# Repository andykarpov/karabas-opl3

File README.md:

## Karabas-OPL3

Simple OPL3 sound card for ZX Spectrum (NemoBus). 
Inspired by a BomgeMoon soundcard :)

### Tech specs

* OPL3 sound by YMF-262-M
* 16-bit DAC UDA1334A
* EPM3128 CPLD
* Low profile PCB: 92x44mm (standard) and 131x44mm (xxl version)
* 5V only power required

### Changelog & current status

* Rev.A - initial release
* Rev.B - reduced pcb size, removed config switch

### Related projects

* BomgeMoon - [link](https://github.com/Kulicheg/BomgeMoon)
* ZX-Multisound - [link](https://github.com/UzixLS/zx-multisound)
* Turbo Sound FM - [link](http://www.nedopc.com/TURBOSOUND/ts-fm.php)
* ZXM-SoundCard - [link](http://micklab.ru/My%20Soundcard/ZXMSoundCard.htm)
* ZXM-GeneralSound - [link](http://micklab.ru/My%20Soundcard/ZXMGeneralSound.htm)
* NeoGS - [link](http://www.nedopc.com/gs/ngs.php)

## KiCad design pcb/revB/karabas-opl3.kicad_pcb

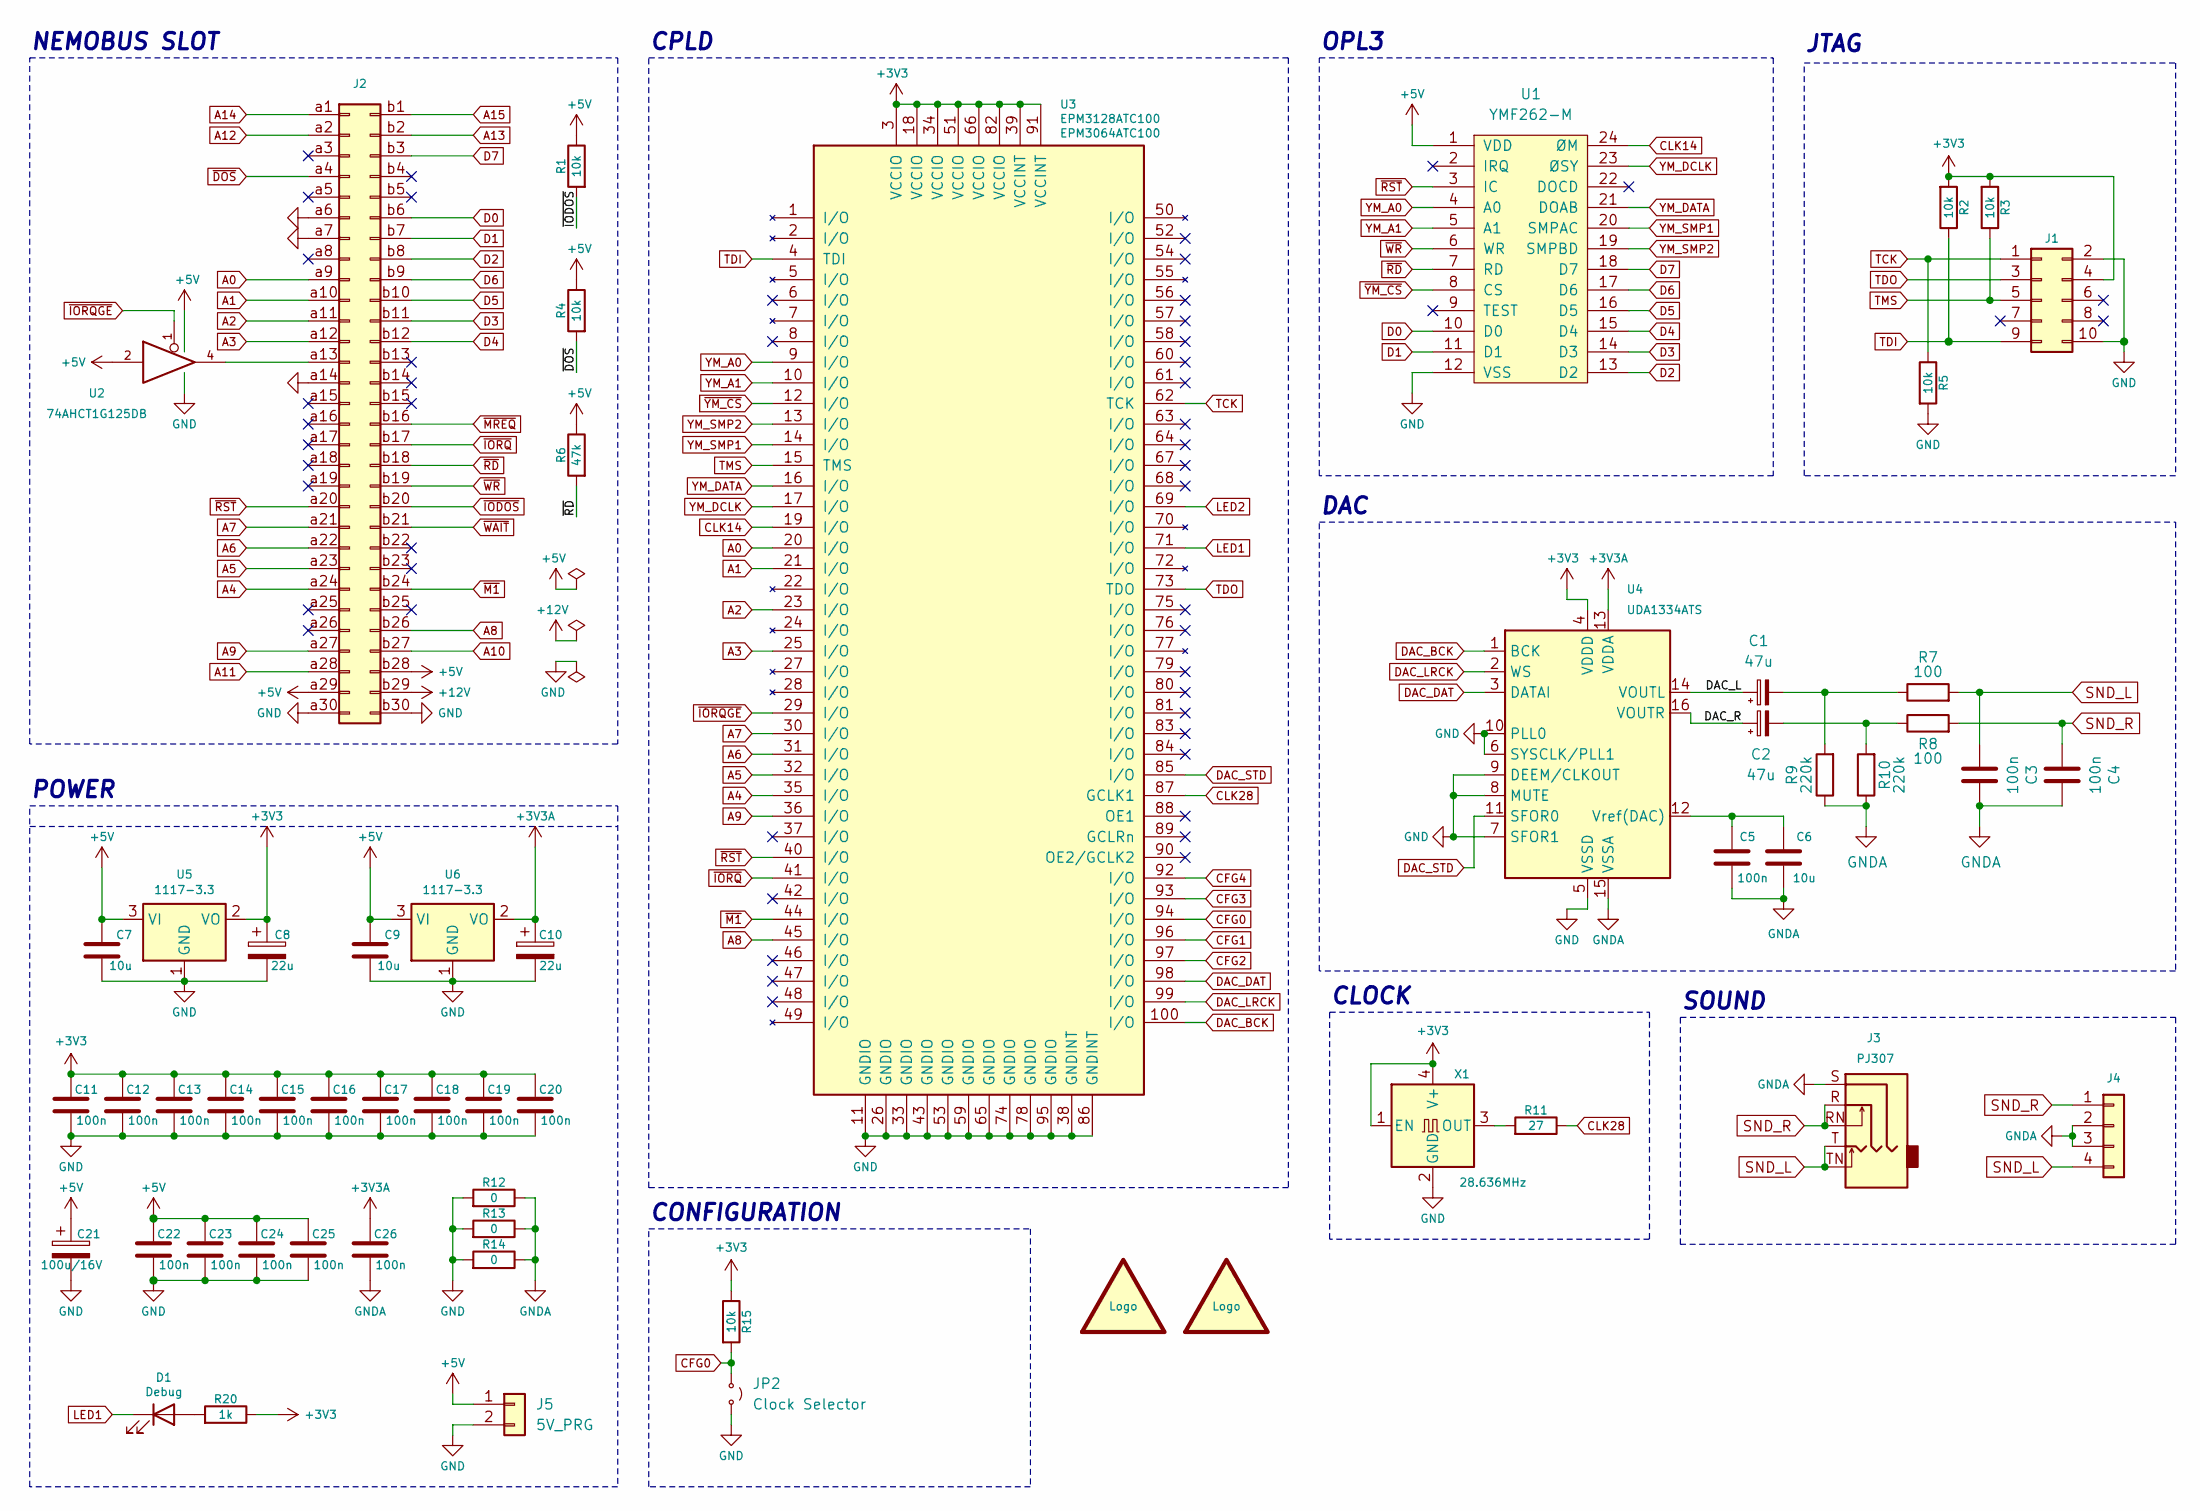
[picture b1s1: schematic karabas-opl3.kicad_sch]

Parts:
C1, C2: 47u; CP_Elec_5x5.9
C3, C4, C5, C11, C12, C13, C14, C15, C16, C17, C18, C19, C20, C22, C23, C24, C25, C26: 100n; C_0805_2012Metric_Pad1.18x1.45mm_HandSolder
C6, C7, C9: 10u; C_0805_2012Metric_Pad1.18x1.45mm_HandSolder
C8, C10: 22u; CP_EIA-3216-18_Kemet-A_HandSolder
C21: 100u/16V; CP_Elec_6.3x7.7
D1: Debug; LED_0805_2012Metric_Pad1.15x1.40mm_HandSolder
J1: Conn_02x05_Odd_Even; PinHeader_2x05_P2.54mm_Vertical
J2: Conn_02x30_Row_Letter_First; ZX_NEMO_60_EDGE
J3: PJ307; PJ-307
J4: Conn_01x04; PinHeader_1x04_P2.54mm_Vertical
J5: 5V_PRG; PinHeader_1x02_P2.54mm_Vertical
JP2: Clock Selector; SolderJumper-2_P1.3mm_Open_TrianglePad1.0x1.5mm
LOGO1: graphic; opl3
LOGO2: graphic; andy_karpov_logo4_silk
R1, R2, R3, R4, R5, R15: 10k; R_0805_2012Metric_Pad1.20x1.40mm_HandSolder
R6: 47k; R_0805_2012Metric_Pad1.20x1.40mm_HandSolder
R7, R8: 100; R_0805_2012Metric_Pad1.20x1.40mm_HandSolder
R9, R10: 220k; R_0805_2012Metric_Pad1.20x1.40mm_HandSolder
R11: 27; R_0805_2012Metric_Pad1.20x1.40mm_HandSolder
R12, R13, R14: 0; R_0805_2012Metric_Pad1.20x1.40mm_HandSolder
R20: 1k; R_0805_2012Metric_Pad1.20x1.40mm_HandSolder
U1: YMF262-M; ymf-262-m
U2: 74AHCT1G125DB; SOT-23-5_HandSoldering
U3: EPM3128ATC100; TQFP-100_14x14mm_P0.5mm
U4: UDA1334ATS; SSOP-16_4.4x5.2mm_P0.65mm-extended
U5, U6: 1117-3.3; SOT-223-3_TabPin2
X1: 28.636MHz; Oscillator_SMD_7050_7.0x5.0mm_mixed_3225

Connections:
+3V3: C8.1, C11.1, C12.1, C13.1, C14.1, C15.1, C16.1, C17.1, C18.1, C19.2, C20.2, J1.4, R2.2, R3.2, R15.1, R20.1, U3.3 (VCCIO), U3.18 (VCCIO), U3.34 (VCCIO), U3.39 (VCCINT), U3.51 (VCCIO), U3.66 (VCCIO), U3.82 (VCCIO), U3.91 (VCCINT), U4.4 (VDDD), U5.2 (VO), X1.1 (EN), X1.4 (V+)
+3V3A: C10.1, C26.1, U4.13 (VDDA), U6.2 (VO)
+5V: C7.1, C9.1, C21.1, C22.2, C23.2, C24.2, C25.2, J2.a29, J2.b28, J5.1, R1.1, R4.1, R6.1, U1.1 (VDD), U2.2, U2.5 (VCC), U5.3 (VI), U6.3 (VI)
+12V: J2.b29
/DAC_L: C1.1, U4.14 (VOUTL)
/DAC_R: C2.1, U4.16 (VOUTR)
A0: J2.a9, U3.20 (I/O)
A1: J2.a10, U3.21 (I/O)
A2: J2.a11, U3.23 (I/O)
A3: J2.a12, U3.25 (I/O)
A4: J2.a24, U3.35 (I/O)
A5: J2.a23, U3.32 (I/O)
A6: J2.a22, U3.31 (I/O)
A7: J2.a21, U3.30 (I/O)
A8: J2.b26, U3.45 (I/O)
A9: J2.a27, U3.36 (I/O)
A10: J2.b27
A11: J2.a28
A12: J2.a2
A13: J2.b2
A14: J2.a1
A15: J2.b1
CFG0: JP2.1 (A), R15.2, U3.94 (I/O)
CFG1: U3.96 (I/O)
CFG2: U3.97 (I/O)
CFG3: U3.93 (I/O)
CFG4: U3.92 (I/O)
CLK14: U1.24 (ØM), U3.19 (I/O)
CLK28: R11.1, U3.87 (GCLK1)
D0: J2.b6, U1.10 (D0)
D1: J2.b7, U1.11 (D1)
D2: J2.b8, U1.13 (D2)
D3: J2.b11, U1.14 (D3)
D4: J2.b12, U1.15 (D4)
D5: J2.b10, U1.16 (D5)
D6: J2.b9, U1.17 (D6)
D7: J2.b3, U1.18 (D7)
DAC_BCK: U3.100 (I/O), U4.1 (BCK)
DAC_DAT: U3.98 (I/O), U4.3 (DATAI)
DAC_LRCK: U3.99 (I/O), U4.2 (WS)
DAC_STD: U3.85 (I/O), U4.11 (SFOR0)
GND: C7.2, C8.2, C9.2, C10.2, C11.2, C12.2, C13.2, C14.2, C15.2, C16.2, C17.2, C18.2, C19.1, C20.1, C21.2, C22.1, C23.1, C24.1, C25.1, J1.2, J1.10, J2.a6, J2.a7, J2.a14, J2.a30, J2.b30, J5.2, JP2.2 (B), R5.2, R12.2, R13.2, R14.2, U1.12 (VSS), U2.3 (GND), U3.11 (GNDIO), U3.26 (GNDIO), U3.33 (GNDIO), U3.38 (GNDINT), U3.43 (GNDIO), U3.53 (GNDIO), U3.59 (GNDIO), U3.65 (GNDIO), U3.74 (GNDIO), U3.78 (GNDIO), U3.86 (GNDINT), U3.95 (GNDIO), U4.5 (VSSD), U4.6 (SYSCLK/PLL1), U4.7 (SFOR1), U4.8 (MUTE), U4.9 (DEEM/CLKOUT), U4.10 (PLL0), U5.1 (GND), U6.1 (GND), X1.2 (GND)
GNDA: C3.2, C4.2, C5.1, C6.1, C26.2, J3.S, J4.2, J4.3, R9.1, R10.1, R12.1, R13.1, R14.1, U4.15 (VSSA)
LED1: D1.1 (K), U3.71 (I/O)
LED2: U3.69 (I/O)
unnamed: C1.2, R7.1, R9.2
unnamed: C2.2, R8.1, R10.2
unnamed: D1.2 (A), R20.2
unnamed: J2.a13, U2.4
unnamed: C5.2, C6.2, U4.12 (Vref(DAC))
unnamed: R11.2, X1.3 (OUT)
SND_L: C3.1, J3.T, J3.TN, J4.4, R7.2
SND_R: C4.1, J3.R, J3.RN, J4.1, R8.2
TCK: J1.1, R5.1, U3.62 (TCK)
TDI: J1.9, R2.1, U3.4 (TDI)
TDO: J1.3, U3.73 (TDO)
TMS: J1.5, R3.1, U3.15 (TMS)
YM_A0: U1.4 (A0), U3.9 (I/O)
YM_A1: U1.5 (A1), U3.10 (I/O)
YM_DATA: U1.21 (DOAB), U3.16 (I/O)
YM_DCLK: U1.23 (ØSY), U3.17 (I/O)
YM_SMP1: U1.20 (SMPAC), U3.14 (I/O)
YM_SMP2: U1.19 (SMPBD), U3.13 (I/O)
~DOS: J2.a4, R4.2
~IODOS: J2.b20, R1.2
~IORQGE: U2.1, U3.29 (I/O)
~IORQ: J2.b17, U3.41 (I/O)
~M1: J2.b24, U3.44 (I/O)
~MREQ: J2.b16
~RD: J2.b18, R6.2, U1.7 (RD)
~RST: J2.a20, U1.3 (IC), U3.40 (I/O)
~WAIT: J2.b21
~WR: J2.b19, U1.6 (WR)
~YM_CS: U1.8 (CS), U3.12 (I/O)

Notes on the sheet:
SOUND
CPLD
DAC
CONFIGURATION
OPL3
JTAG
POWER
CLOCK
NEMOBUS SLOT

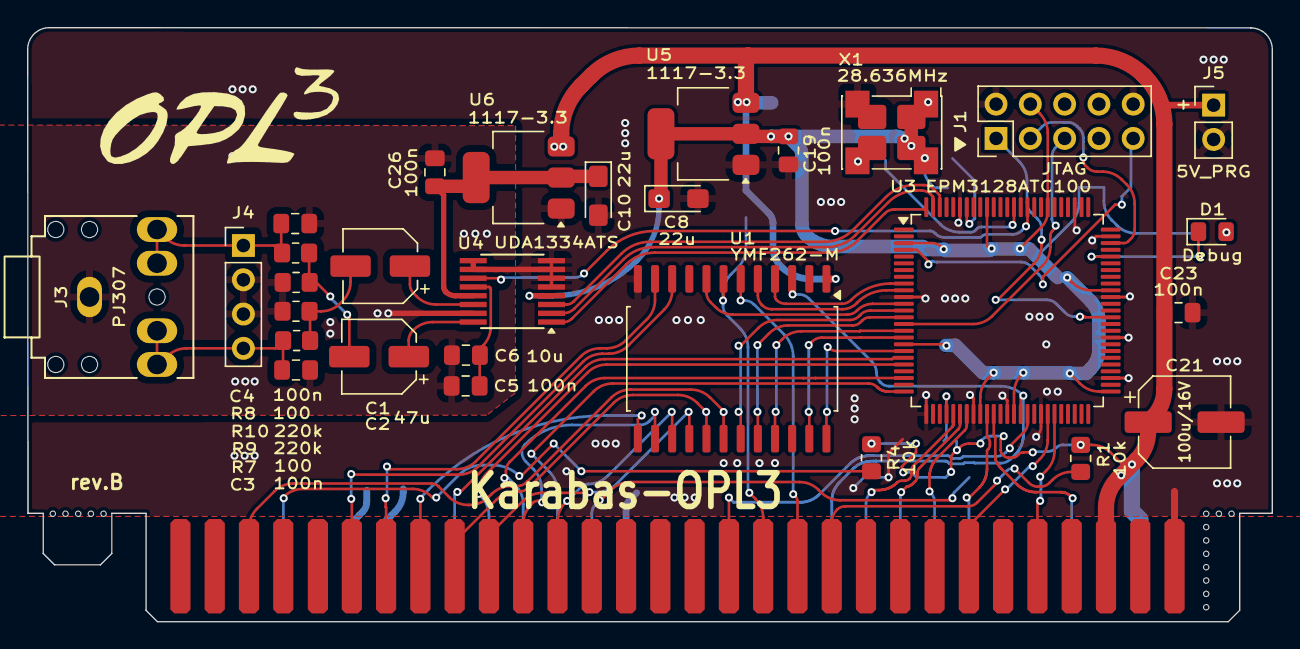
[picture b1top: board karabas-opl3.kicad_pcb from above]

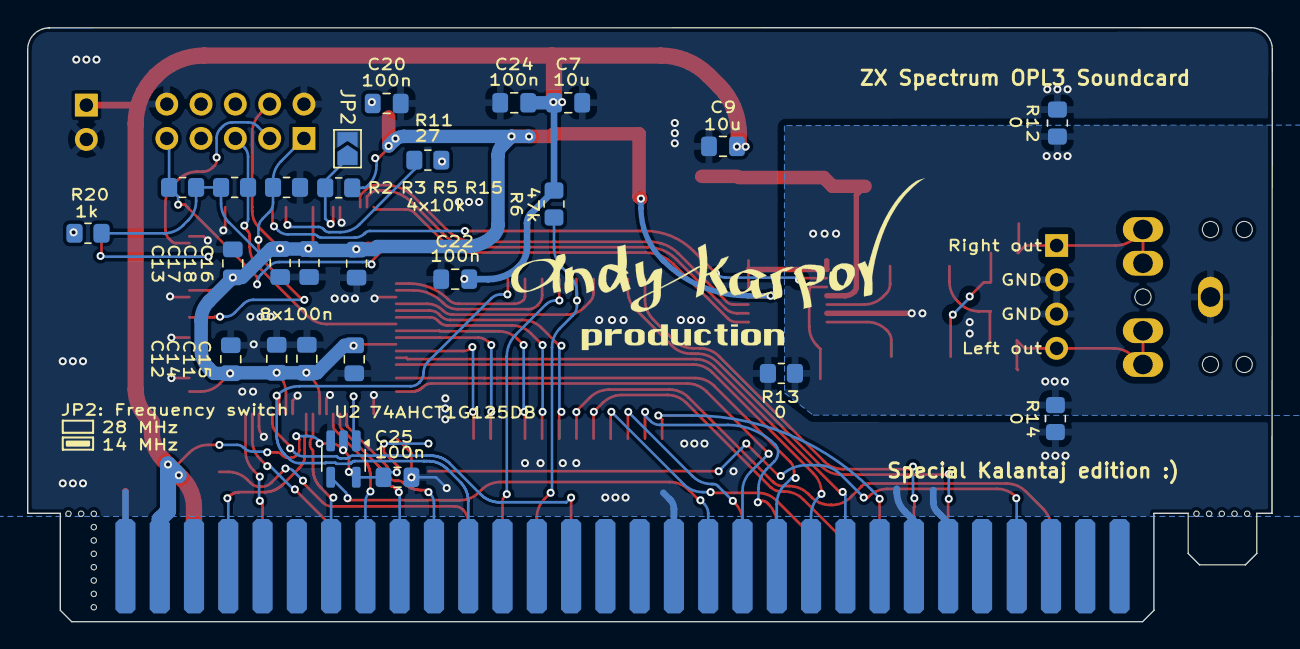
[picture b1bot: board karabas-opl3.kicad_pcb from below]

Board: 2 copper layers, 92.2 x 44.0 mm, 58 parts (27 on the bottom side), 60 nets.

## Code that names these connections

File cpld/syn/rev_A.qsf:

# -------------------------------------------------------------------------- #
#
# Copyright (C) 1991-2013 Altera Corporation
# Your use of Altera Corporation's design tools, logic functions 
# and other software and tools, and its AMPP partner logic 
# functions, and any output files from any of the foregoing 
# (including device programming or simulation files), and any 
# associated documentation or information are expressly subject 
# to the terms and conditions of the Altera Program License 
# Subscription Agreement, Altera MegaCore Function License 
# Agreement, or other applicable license agreement, including, 
# without limitation, that your use is for the sole purpose of 
# programming logic devices manufactured by Altera and sold by 
# Altera or its authorized distributors.  Please refer to the 
# applicable agreement for further details.
#
# -------------------------------------------------------------------------- #
#
# Quartus II 64-Bit
# Version 13.0.1 Build 232 06/12/2013 Service Pack 1 SJ Full Version
# Date created = 12:04:27  October 04, 2020
#
# -------------------------------------------------------------------------- #
#
# Notes:
#
# 1) The default values for assignments are stored in the file:
#		zx_multisound_assignment_defaults.qdf
#    If this file doesn't exist, see file:
#		assignment_defaults.qdf
#
# 2) Altera recommends that you do not modify this file. This
#    file is updated automatically by the Quartus II software
#    and any changes you make may be lost or overwritten.
#
# -------------------------------------------------------------------------- #


set_global_assignment -name FAMILY MAX3000A
set_global_assignment -name DEVICE "EPM3128ATC100-10"
set_global_assignment -name TOP_LEVEL_ENTITY karabas_opl3
set_global_assignment -name ORIGINAL_QUARTUS_VERSION "13.0 SP1"
set_global_assignment -name PROJECT_CREATION_TIME_DATE "12:04:27  OCTOBER 04, 2020"
set_global_assignment -name LAST_QUARTUS_VERSION "13.0 SP1"
set_global_assignment -name PROJECT_OUTPUT_DIRECTORY output
set_global_assignment -name DEVICE_FILTER_PIN_COUNT 144
set_global_assignment -name ERROR_CHECK_FREQUENCY_DIVISOR "-1"
set_global_assignment -name SDC_FILE clocks.sdc
set_global_assignment -name VERILOG_FILE ../rtl/top.v
set_global_assignment -name VHDL_INPUT_VERSION VHDL_2008
set_global_assignment -name VHDL_SHOW_LMF_MAPPING_MESSAGES OFF
set_global_assignment -name VERILOG_INPUT_VERSION VERILOG_2001
set_global_assignment -name VERILOG_SHOW_LMF_MAPPING_MESSAGES OFF
set_global_assignment -name MAX7000_DEVICE_IO_STANDARD "3.3-V LVTTL"
set_global_assignment -name SAVE_DISK_SPACE OFF
set_global_assignment -name TIMEQUEST_MULTICORNER_ANALYSIS OFF
set_global_assignment -name SYNTH_TIMING_DRIVEN_SYNTHESIS OFF

set_location_assignment PIN_9 -to ym_a[0]
set_location_assignment PIN_10 -to ym_a[1]
set_location_assignment PIN_12 -to n_ym_cs
set_location_assignment PIN_13 -to ym_smp[1]
set_location_assignment PIN_16 -to ym_data
set_location_assignment PIN_17 -to ym_dclk
set_location_assignment PIN_19 -to clk14
set_location_assignment PIN_20 -to a[0]
set_location_assignment PIN_21 -to a[1]
set_location_assignment PIN_23 -to a[2]
set_location_assignment PIN_29 -to n_iorqge
set_location_assignment PIN_30 -to a[7]
set_location_assignment PIN_31 -to a[6]
set_location_assignment PIN_32 -to a[5]
set_location_assignment PIN_35 -to a[4]
set_location_assignment PIN_36 -to a[9]
set_location_assignment PIN_41 -to n_iorq
set_location_assignment PIN_44 -to n_m1
set_location_assignment PIN_45 -to a[8]
set_location_assignment PIN_87 -to clk28
set_location_assignment PIN_92 -to cfg[4]
set_location_assignment PIN_93 -to cfg[3]
set_location_assignment PIN_94 -to cfg[0]
set_location_assignment PIN_96 -to cfg[1]
set_location_assignment PIN_97 -to cfg[2]
set_location_assignment PIN_98 -to dac_dat
set_location_assignment PIN_99 -to dac_lrck
set_location_assignment PIN_100 -to dac_bck

set_global_assignment -name MAX7000_OPTIMIZATION_TECHNIQUE BALANCED
set_global_assignment -name PRE_MAPPING_RESYNTHESIS OFF
set_global_assignment -name OPTIMIZE_HOLD_TIMING OFF
set_global_assignment -name OPTIMIZE_MULTI_CORNER_TIMING ON
set_global_assignment -name FITTER_EFFORT "STANDARD FIT"
set_global_assignment -name RESERVE_ALL_UNUSED_PINS_NO_OUTPUT_GND "AS INPUT TRI-STATED"

set_location_assignment PIN_14 -to ym_smp[0]
set_location_assignment PIN_85 -to dac_std
set_location_assignment PIN_71 -to led[0]
set_location_assignment PIN_69 -to led[1]
set_location_assignment PIN_25 -to a[3]
set_location_assignment PIN_40 -to n_rst
set_instance_assignment -name GLOBAL_SIGNAL "GLOBAL CLOCK" -to clk28

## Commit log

2025-07-25 initial commit, revA
2025-07-25 Updated references
2025-07-25 Initial cpld firmware
2025-07-26 Added debug leds
2025-07-26 Added cpld firmware
2025-07-26 Added pof
2025-07-26 Updated docs
2025-07-26 Added renders
2025-07-26 Latest changes
2025-07-27 Added pj307 3d model
2025-08-06 Added universal footprint for 3225+5070 osc
2025-08-06 Updated 5V lane - removed loop
2025-09-17 Added testbench
2025-09-17 First working sw revision
2025-09-17 Gitignore
2025-09-17 Fixed amplitude
2025-09-17 Small footprint fixes
2025-09-17 Latest firmware release
2025-09-17 Updated revA renders
2025-09-17 Added gtkw
2025-09-18 Rev.B
2025-09-18 Updated makefile
2025-09-18 Updated License
2025-09-18 Updated revB gerbers
2025-09-18 removed cfg switches, keep only one to select oscillator frequency
2025-09-18 Code cleanup
2025-09-18 revB-xxl
2025-09-18 Inverted the cfg jumper to be compatible with revB
2025-09-18 Fixed measures for rev.B
